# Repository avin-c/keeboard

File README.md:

# Keyz
My custom 65% mechanical keyboard as part of [Hack Club's Keeb YSWS](https://keeb.hackclub.com/). Hours spent is in the [Journal.md](Journal.md)

## Description

My keyboard "Keyz" is a 65% mechanical keyboard powered by a Raspberry Pi Pico microcontroller. It uses the classic Gateron Quinn switches for a subtle tactile click, and is intended to be minimalistic with a compact layout while also providing the full functionality that an average keyboard user would need. It uses a sandwich mount to house the PCB, and features a rotary encoder to be used as volume control.

## Why I made it

I made this keyboard not because I percisely needed one, but because I had always dreamed of having a mechanical keyboard, but having a laptop did not pose a need to purchase one. Instead, I decided to create one instead. Another reason I chose to create this keyboard is because I am very interested in learning more about electronics and hardware, so I thought making a keyboard would be one of the best ways to get my feet wet. Anyways, this keyboard inspired me to make more projects, because it was so satisfying to go through the steps and end up with a full keyboard (at least in Onshape, I haven't actually built it yet). 

## Learning process

I learnt so much through the process of making this keyboard. I started off this project knowing absolutely nothing about keyboards at all, and know I have learnt how they work, the inner mechanisms, different types of casing, and how they are wired. In addiition, I also didn't know anything about KiCad before this project, but making this keyboard gave me a chance to learn how making a PCB works from the schematic to wiring up all the connections. It kinda surprised me how crazy the initial schematic to PCB stage was (it was VERY messy), and I was completely overwhelmed by the number of wires and connections. However, I managed to get through it and would consider myself having a solid beginner-level understanding of KiCad! I already knew about Onshape, but I definitely explored some new features in this project, like editing in context. 

Another thing this project taught me was how iterative the engineering process is, because I had a major hiccup when I thought I was almost done and got to buying keycaps, I realized that my switch sizes were not standard, and would entail 3d printing custom keycaps, which I didnt like the quality of. So I had to basically repeat the whole project with the schematic and the PCB to change the layout so that my keycap sizes were standard and fit the keycap set I was buying. 

Overall, this project was incredibly fun and taught me so much that I hope to apply in future projects. 

## Bill Of Materials 

[Link](https://docs.google.com/spreadsheets/d/1fL_IQgmIi_XlOX9ydgWSfowry5usrP5Ks7BfyhSlTqM/edit?gid=0#gid=0) to the BOM in Google Sheets with most updated info. 

| Category | Item | Quantity | Unit Cost (CAD) | Total Cost (CAD) | Total Cost (USD) | Supplier |
|---|---|---:|---:|---:|---:|---|
| Electronics | EC11 Rotary Encoder | 1 | $4.44 | $4.44 | $3.22 | [DigiKey](https://www.digikey.ca/en/products/detail/bourns-inc/PEC11R-4215K-S0024/4499662) |
|  | 1N4148 Diode | 100 | $0.54 | $5.43 | $3.93 | [DigiKey](https://www.digikey.ca/short/thzf78m3) |
|  | Raspberry Pi Pico | 1 | $5.65 | $5.65 | $4.09 | [Pishop](https://www.pishop.ca/product/raspberry-pi-pico-non-wireless/?src=raspberrypi) |
|  | Header Set | 1 | $2.45 | $2.45 | $1.77 | [Pishop](https://www.pishop.ca/product/raspberry-pi-pico-header-set/) |
| PCB | PCB | 5 | $5.74 | $28.70 | $20.79 | JLCPCB |
| Case accessories | M2.5 Heatset Insert | 6 | $0.29 | $1.74 | $1.26 | [DigiKey](https://www.digikey.ca/short/qzncdpv7) |
|   | M2.5 Screw | 6 | $0.18 | $1.10 | $0.80 | [DigiKey](https://www.digikey.ca/short/h5w2dz84) |
|   | Rubber Pads | 10 | $0.42 | $4.20 | $3.04 | [AliExpress](https://www.aliexpress.com/item/1005009215190070.html) |
| Keyboard | Gateron Quinn Switches | 2 | $25.92 | $51.84 | $37.56 | [Best Buy](https://www.bestbuy.ca/en-ca/product/gateron-quinn-keyboard-switches-tactile-59gf-rgb-5-pin-pre-lubed-for-mx-mechanical-gaming-keyboard-35pcs/19677735) |
|  | MX Stabilizers | 1 | $12.39 | $12.39 | $8.98 | [AliExpress](https://www.aliexpress.com/item/1005011961905061.html?pdp_ext_f=%7B%22order%22%3A%224%22%2C%22spu_best_type%22%3A%22price%22%2C%22eval%22%3A%221%22%2C%22fromPage%22%3A%22search%22%7D) |
|  | Keycaps | 1 | $33.89 | $33.89 | $24.55 | [Amazon](https://www.amazon.ca/KBDiy-Keycaps-Percent-Mechanical-Keyboard/dp/B0CT5C2B8F/ref=sr_1_12?crid=1G9HY1UQNN4EB&dib=eyJ2IjoiMSJ9.clPrYS9Mkyt7Ng5yimc05HMOhgR_GEZWlov_hXIkV9-_h0WDo9gYInM0Yk9tMJwczcDFMajBQryI1t6EV9p5ITevjSiprSjUviSEQx3G5hNPEWnSzGRGL956B40tmiqJm-n2AawS38tOLG-GFsVDaeSjmj9awOJeDdH045WScT0GTN6IsGh-ItvRhL_881FHrDxEOcqkqGO3Dg4sBr-J1XczmzxubBDGn-RJNlNZkypSSrn-67t4XAXXBuu6ufBuBYeUX3MqzMp8gpuCwUrFE91R8SOQ8tcxfq_Ag4yXTtg.RBzHkodv9L72tgKA8IOQ7Xk_Ys0xNDpOGra9LuzEhMY&dib_tag=se&keywords=blue%2Bkeycap%2Bset&qid=1786037838&s=electronics&sprefix=blue%2Bkeycap%2Bset%2Celectronics%2C122&sr=1-12&th=1) |
| Shipping | Pishop Shipping | — | $13.01 | $13.01 | $9.43 | Pishop |
|  | JLCPCB Shipping | — | $41.67 | $41.67 | $30.19 | JLCPCB |
|  | DigiKey Shipping | — | $15.00 | $15.00 | $10.87 | DigiKey |
|  | AliExpress Shipping | — | $7.34 | $7.34 | $5.32 | AliExpress |
| **Total** | | | | **$228.85 CAD** | **$165.79 USD** | |

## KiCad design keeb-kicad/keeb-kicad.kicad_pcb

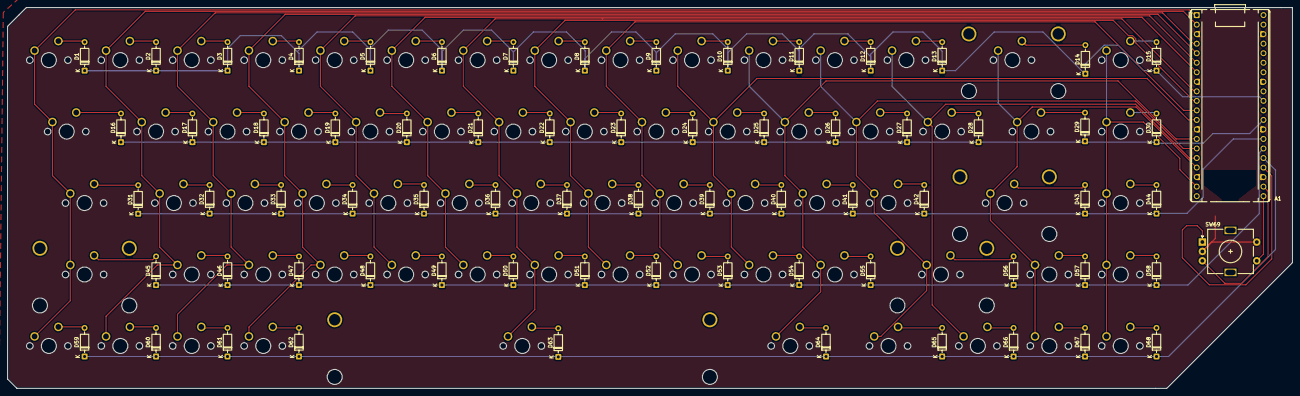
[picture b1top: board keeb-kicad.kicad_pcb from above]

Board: 2 copper layers, 342.5 x 101.5 mm, 143 parts (0 on the bottom side), 92 nets.

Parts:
A1: RaspberryPi_Pico; RaspberryPi_Pico_Common_THT
D1, D2, D3, D4, D5, D6, D7, D8, D9, D10, D11, D12, D13, D14, D15, D16, D17, D18, D19, D20, D21, D22, D23, D24, D25, D26, D27, D28, D29, D30, D31, D32, D33, D34, D35, D36, D37, D38, D39, D40, D41, D42, D43, D44, D45, D46, D47, D48, D49, D50, D51, D52, D53, D54, D55, D56, D57, D58, D59, D60, D61, D62, D63, D64, D65, D66, D67, D68: 1N4148; D_DO-35_SOD27_P7.62mm_Horizontal
S1, S2, S3: MX_stab; STAB_MX_P_2u
S4: MX_stab; STAB_MX_P_2.25u
S5: MX_stab; STAB_MX_P_6.25u
SW1, SW2, SW3, SW4, SW5, SW6, SW7, SW8, SW9, SW10, SW11, SW12, SW13, SW14, SW15, SW16, SW17, SW18, SW19, SW20, SW21, SW22, SW23, SW24, SW25, SW26, SW27, SW28, SW29, SW30, SW31, SW32, SW33, SW34, SW35, SW36, SW37, SW38, SW39, SW40, SW41, SW42, SW43, SW44, SW45, SW46, SW47, SW48, SW49, SW50, SW51, SW52, SW53, SW54, SW55, SW56, SW57, SW58, SW59, SW60, SW61, SW62, SW63, SW64, SW65, SW66, SW67, SW68: SW_Push; SW_MX_1u
SW69: RotaryEncoder_Switch; RotaryEncoder_Alps_EC11E-Switch_Vertical_H20mm

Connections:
/COL0: A1.1 (GPIO0), SW1.1, SW16.1, SW31.1, SW45.1, SW59.1
/COL1: A1.2 (GPIO1), SW2.1, SW17.1, SW32.1, SW46.1, SW60.1
/COL2: A1.4 (GPIO2), SW3.1, SW18.1, SW33.1, SW47.1, SW61.1
/COL3: A1.5 (GPIO3), SW4.1, SW19.1, SW34.1, SW48.1, SW62.1
/COL4: A1.6 (GPIO4), SW5.1, SW20.1, SW35.1, SW49.1
/COL5: A1.7 (GPIO5), SW6.1, SW21.1, SW36.1, SW50.1
/COL6: A1.9 (GPIO6), SW7.1, SW22.1, SW37.1, SW51.1, SW63.1
/COL7: A1.10 (GPIO7), SW8.1, SW23.1, SW38.1, SW52.1
/COL8: A1.11 (GPIO8), SW9.1, SW24.1, SW39.1, SW53.1
/COL9: A1.12 (GPIO9), SW10.1, SW25.1, SW40.1, SW54.1
/COL10: A1.14 (GPIO10), SW11.1, SW26.1, SW41.1, SW55.1, SW64.1
/COL11: A1.15 (GPIO11), SW12.1, SW27.1, SW42.1, SW56.1, SW65.1
/COL12: A1.16 (GPIO12), SW13.1, SW28.1, SW66.1
/COL13: A1.17 (GPIO13), SW14.1, SW29.1, SW43.1, SW57.1, SW67.1
/COL14: A1.19 (GPIO14), SW15.1, SW30.1, SW44.1, SW58.1, SW68.1
/ENC_A: A1.24 (GPIO18), SW69.A
/ENC_B: A1.22 (GPIO17), SW69.B
/ROW0: A1.31 (GPIO26_ADC0), D1.1 (K), D2.1 (K), D3.1 (K), D4.1 (K), D5.1 (K), D6.1 (K), D7.1 (K), D8.1 (K), D9.1 (K), D10.1 (K), D11.1 (K), D12.1 (K), D13.1 (K), D14.1 (K), D15.1 (K)
/ROW1: A1.29 (GPIO22), D16.1 (K), D17.1 (K), D18.1 (K), D19.1 (K), D20.1 (K), D21.1 (K), D22.1 (K), D23.1 (K), D24.1 (K), D25.1 (K), D26.1 (K), D27.1 (K), D28.1 (K), D29.1 (K), D30.1 (K)
/ROW2: A1.27 (GPIO21), D31.1 (K), D32.1 (K), D33.1 (K), D34.1 (K), D35.1 (K), D36.1 (K), D37.1 (K), D38.1 (K), D39.1 (K), D40.1 (K), D41.1 (K), D42.1 (K), D43.1 (K), D44.1 (K)
/ROW3: A1.26 (GPIO20), D45.1 (K), D46.1 (K), D47.1 (K), D48.1 (K), D49.1 (K), D50.1 (K), D51.1 (K), D52.1 (K), D53.1 (K), D54.1 (K), D55.1 (K), D56.1 (K), D57.1 (K), D58.1 (K)
/ROW4: A1.25 (GPIO19), D59.1 (K), D60.1 (K), D61.1 (K), D62.1 (K), D63.1 (K), D64.1 (K), D65.1 (K), D66.1 (K), D67.1 (K), D68.1 (K)
/SWITCH1: A1.21 (GPIO16), SW69.S1
GND: A1.3 (GND), A1.8 (GND), A1.13 (GND), A1.18 (GND), A1.23 (GND), A1.28 (GND), A1.38 (GND), SW69.C, SW69.S2
unnamed: D1.2 (A), SW1.2
unnamed: D2.2 (A), SW2.2
unnamed: D3.2 (A), SW3.2
unnamed: D4.2 (A), SW4.2
unnamed: D5.2 (A), SW5.2
unnamed: D6.2 (A), SW6.2
unnamed: D7.2 (A), SW7.2
unnamed: D8.2 (A), SW8.2
unnamed: D9.2 (A), SW9.2
unnamed: D10.2 (A), SW10.2
unnamed: D11.2 (A), SW11.2
unnamed: D12.2 (A), SW12.2
unnamed: D13.2 (A), SW13.2
unnamed: D14.2 (A), SW14.2
unnamed: D15.2 (A), SW15.2
unnamed: D16.2 (A), SW16.2
unnamed: D17.2 (A), SW17.2
unnamed: D18.2 (A), SW18.2
unnamed: D19.2 (A), SW19.2
unnamed: D20.2 (A), SW20.2
unnamed: D21.2 (A), SW21.2
unnamed: D22.2 (A), SW22.2
unnamed: D23.2 (A), SW23.2
unnamed: D24.2 (A), SW24.2
unnamed: D25.2 (A), SW25.2
unnamed: D26.2 (A), SW26.2
unnamed: D27.2 (A), SW27.2
unnamed: D28.2 (A), SW28.2
unnamed: D29.2 (A), SW29.2
unnamed: D30.2 (A), SW30.2
unnamed: D31.2 (A), SW31.2
unnamed: D32.2 (A), SW32.2
unnamed: D33.2 (A), SW33.2
unnamed: D34.2 (A), SW34.2
unnamed: D35.2 (A), SW35.2
unnamed: D36.2 (A), SW36.2
unnamed: D37.2 (A), SW37.2
unnamed: D38.2 (A), SW38.2
unnamed: D39.2 (A), SW39.2
unnamed: D40.2 (A), SW40.2
unnamed: D41.2 (A), SW41.2
unnamed: D42.2 (A), SW42.2
unnamed: D43.2 (A), SW43.2
unnamed: D44.2 (A), SW44.2
unnamed: D45.2 (A), SW45.2
unnamed: D46.2 (A), SW46.2
unnamed: D47.2 (A), SW47.2
unnamed: D48.2 (A), SW48.2
unnamed: D49.2 (A), SW49.2
unnamed: D50.2 (A), SW50.2
unnamed: D51.2 (A), SW51.2
unnamed: D52.2 (A), SW52.2
unnamed: D53.2 (A), SW53.2
unnamed: D54.2 (A), SW54.2
unnamed: D55.2 (A), SW55.2
unnamed: D56.2 (A), SW56.2
unnamed: D57.2 (A), SW57.2
unnamed: D58.2 (A), SW58.2
unnamed: D59.2 (A), SW59.2
unnamed: D60.2 (A), SW60.2
unnamed: D61.2 (A), SW61.2
unnamed: D62.2 (A), SW62.2
unnamed: D63.2 (A), SW63.2
unnamed: D64.2 (A), SW64.2
unnamed: D65.2 (A), SW65.2
unnamed: D66.2 (A), SW66.2
unnamed: D67.2 (A), SW67.2
unnamed: D68.2 (A), SW68.2
